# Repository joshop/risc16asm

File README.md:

# RISC-16

Assembler, emulator, and HDL for a custom 16-bit RISC-based instruction set.

## Usage

### Assembly

Suppose we have assembly code in `scripts/test_1.asm`. To assemble it into machine code:

```sh
python src/assemble.py scripts/test_1.asm [-o <output_file>]
```

If no output file is specified, it will default to `<basename>.bin`.

### Emulation

If the machine code is in `scripts/test_1.bin`, emulate it using

```sh
python src/interpret.py scripts/test_1.bin
```

### All-in-one

To do it all in one step, run

```sh
python src/run.py scripts/test_1.asm
```

## Assembly format

A program consists of a sequence of the following separated by newlines:

- Instructions of the form `op field, ...`, which emit their opcode
- Labels of the form `lab: `, which defines `lab` to be the current address
- Comments of the form `// comment text ended by a newline`
- Whitespace (which is ignored)
- Assembler directives
- Macros

Assembler directives include the following:

- `.word X` emits a single word (16 bits), `X`
- `.dword X` emits a double word (32 bits), `X`
- `.def Y X` defines a constant with value `X` called `Y`
- `.addr X` defines the current address to be `X`
- `.bin filename` emits all of the bytes in `filename`
- `.include filename` causes the assembler to process `filename`'s contents as if it was inserted into the file directly.
- `.macro pattern` defines a macro that translates any statement matched by the regex `pattern`. Statements until `.endmacro` are considered part of the macro. Macros can contain sub-macros that are already defined, as well as `.bin` and `.include` directives.

When instructions are assembled, immediates can be expressions with any of the following components:

- Constants in decimal, hexadecimal (`$` or `0x`) prefix, binary (`%` or `0b` prefix)
- Constants defined with `.def`
- Addresses of labels within the program
- `+`, `-`, `&`, `|`, `^`, `~`, `>>`, `<<` operators
  Example:

```
.macro li (r[0-7]), ([0-9]+)
lui \1, (\2) >> 8
addi \1, \1, (\2) & $ff
.endmacro
.addr 0
main:
  li r3, myfunction
  jalr r0, r3
.addr $1234
myfunction:
  // ... do something
```

Notes on syntax:

- `ecall <code>` can be used to trigger special hardware functions. They get encoded as a `jalr` instruction with nonzero immediate. The web interpreter is currently configured for the following ecall codes:
  - `1`: refresh display

## HDL

A SystemVerilog implementation of a CPU running this assembly exists in `src/hdl/`. Testbenches for this implementation exist in `src/hdl_sim/`.

## TODO

- [ ] Fix include file path tracing
- [ ] Figure out how context stuff works with respect to `.include` directives and document it

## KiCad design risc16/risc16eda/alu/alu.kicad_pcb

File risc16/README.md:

# RISC-16

Assembler, emulator, and HDL for a custom 16-bit RISC-based instruction set.

## Usage

### Assembly

Suppose we have assembly code in `scripts/test_1.asm`. To assemble it into machine code:

```sh
python src/assemble.py scripts/test_1.asm [-o <output_file>]
```

If no output file is specified, it will default to `<basename>.bin`.

### Emulation

If the machine code is in `scripts/test_1.bin`, emulate it using

```sh
python src/interpret.py scripts/test_1.bin
```

### All-in-one

To do it all in one step, run

```sh
python src/run.py scripts/test_1.asm
```

## Assembly format

A program consists of a sequence of the following separated by newlines:

- Instructions of the form `op field, ...`, which emit their opcode
- Labels of the form `lab: `, which defines `lab` to be the current address
- Comments of the form `// comment text ended by a newline`
- Whitespace (which is ignored)
- Assembler directives
- Macros

Assembler directives include the following:

- `.word X` emits a single word (16 bits), `X`
- `.dword X` emits a double word (32 bits), `X`
- `.def Y X` defines a constant with value `X` called `Y`
- `.addr X` defines the current address to be `X`
- `.bin filename` emits all of the bytes in `filename`
- `.include filename` causes the assembler to process `filename`'s contents as if it was inserted into the file directly.
- `.macro pattern` defines a macro that translates any statement matched by the regex `pattern`. Statements until `.endmacro` are considered part of the macro. Macros can contain sub-macros that are already defined, as well as `.bin` and `.include` directives.

When instructions are assembled, immediates can be expressions with any of the following components:

- Constants in decimal, hexadecimal (`$` or `0x`) prefix, binary (`%` or `0b` prefix)
- Constants defined with `.def`
- Addresses of labels within the program
- `+`, `-`, `&`, `|`, `^`, `~`, `>>`, `<<` operators
  Example:

```
.macro li (r[0-7]), ([0-9]+)
lui \1, (\2) >> 8
addi \1, \1, (\2) & $ff
.endmacro
.addr 0
main:
  li r3, myfunction
  jalr r0, r3
.addr $1234
myfunction:
  // ... do something
```

Notes on syntax:

- `ecall <code>` can be used to trigger special hardware functions. They get encoded as a `jalr` instruction with nonzero immediate. The web interpreter is currently configured for the following ecall codes:
  - `1`: refresh display

## HDL

A SystemVerilog implementation of a CPU running this assembly exists in `src/hdl/`. Testbenches for this implementation are in `src/hdl_sim/`.

## TODO

- [ ] Fix include file path tracing
- [ ] Figure out how context stuff works with respect to `.include` directives and document it

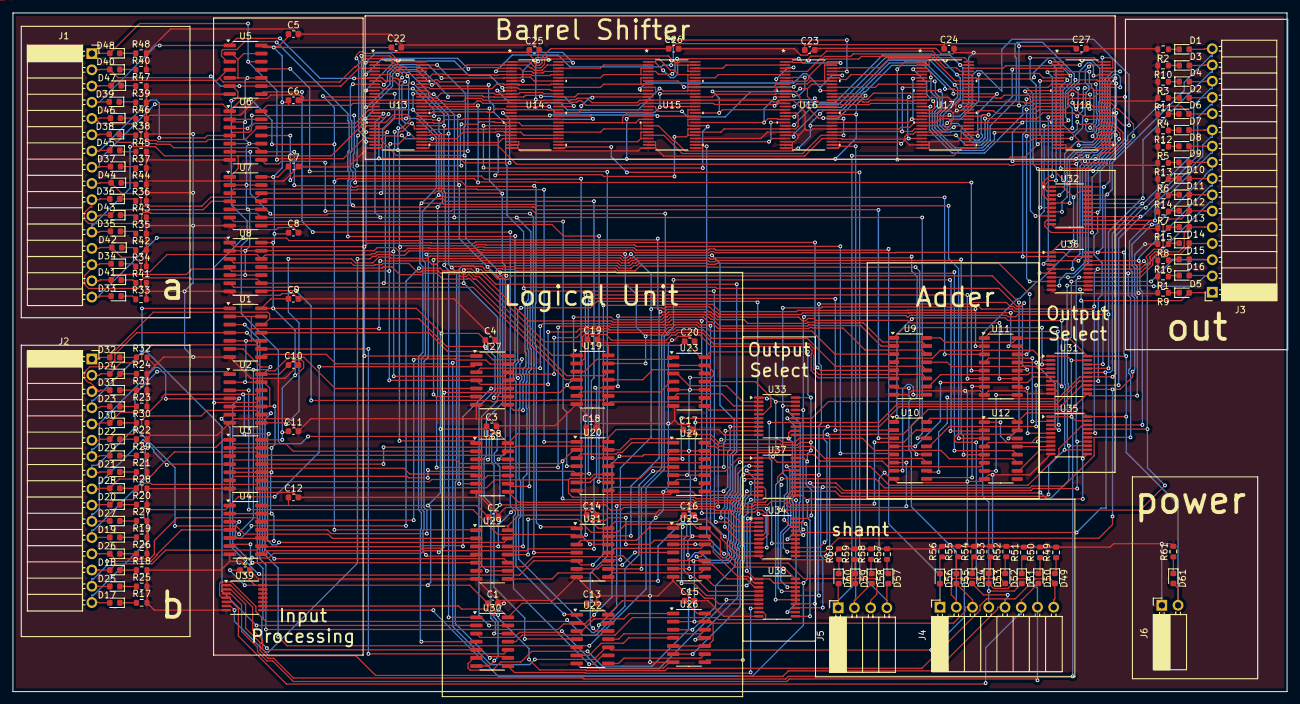
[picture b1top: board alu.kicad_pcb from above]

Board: 2 copper layers, 199.4 x 106.2 mm, 194 parts (0 on the bottom side), 322 nets.

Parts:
C1, C2, C3, C4, C5, C6, C7, C8, C9, C10, C11, C12, C13, C14, C15, C16, C17, C18, C19, C20, C22, C23, C24, C25, C26, C27: 0.1u; C_0603_1608Metric
C21: C; C_0603_1608Metric
D1, D2, D3, D4, D5, D6, D7, D8, D9, D10, D11, D12, D13, D14, D15, D16, D17, D18, D19, D20, D21, D22, D23, D24, D25, D26, D27, D28, D29, D30, D31, D32, D33, D34, D35, D36, D37, D38, D39, D40, D41, D42, D43, D44, D45, D46, D47, D48, D49, D50, D51, D52, D53, D54, D55, D56, D57, D58, D59, D60, D61: LED; LED_0603_1608Metric
J1, J2, J3: Conn_01x16; PinSocket_1x16_P2.54mm_Horizontal
J4: Conn_01x08; PinSocket_1x08_P2.54mm_Horizontal
J5: Conn_01x04; PinSocket_1x04_P2.54mm_Horizontal
J6: Conn_01x02; PinSocket_1x02_P2.54mm_Horizontal
R1, R2, R3, R4, R5, R6, R7, R8, R9, R10, R11, R12, R13, R14, R15, R16, R17, R18, R19, R20, R21, R22, R23, R24, R25, R26, R27, R28, R29, R30, R31, R32, R33, R34, R35, R36, R37, R38, R39, R40, R41, R42, R43, R44, R45, R46, R47, R48, R49, R50, R51, R52, R53, R54, R55, R56, R57, R58, R59, R60, R61: 1k; R_0603_1608Metric
U1, U2, U3, U4, U5, U6, U7, U8, U23, U24, U25, U26, U27, U28, U29, U30: 74HC86; SO-14_3.9x8.65mm_P1.27mm
U9, U10, U11, U12: 74LS283; SO-16_3.9x9.9mm_P1.27mm
U13, U14, U15, U16, U17, U18: SN74CBT16233DGGR; DGG56
U19, U20, U21, U22: 74HC00; SO-14_3.9x8.65mm_P1.27mm
U31, U32, U33, U34, U35, U36, U37, U38: 74AHC541; TSSOP-20_4.4x6.5mm_P0.65mm
U39: 74HC04; TSSOP-14_4.4x5mm_P0.65mm

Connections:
/!isAddSub: U31.1 (G1), U31.19 (G2), U35.1 (G1), U35.19 (G2), U39.2
/!isNand: U33.1 (G1), U33.19 (G2), U37.1 (G1), U37.19 (G2), U39.4
/!isShift: U32.1 (G1), U32.19 (G2), U36.1 (G1), U36.19 (G2), U39.6
/!isXor: U34.1 (G1), U34.19 (G2), U38.1 (G1), U38.19 (G2), U39.8
/A0: D33.2 (A), J1.16, U8.1, U9.5 (A1), U13.26 (16B2), U13.56 (1B1), U27.1
/A1: D41.2 (A), J1.15, U8.4, U9.3 (A2), U13.2 (2B1), U13.32 (15B2), U27.4
/A2: D34.2 (A), J1.14, U8.9, U9.14 (A3), U13.23 (14B2), U13.53 (3B1), U27.9
/A3: D42.2 (A), J1.13, U8.12, U9.12 (A4), U13.5 (4B1), U13.35 (13B2), U27.12
/A4: D35.2 (A), J1.12, U7.1, U10.5 (A1), U13.20 (12B2), U13.50 (5B1), U28.1
/A5: D43.2 (A), J1.11, U7.4, U10.3 (A2), U13.8 (6B1), U13.38 (11B2), U28.4
/A6: D36.2 (A), J1.10, U7.9, U10.14 (A3), U13.17 (10B2), U13.47 (7B1), U28.9
/A7: D44.2 (A), J1.9, U7.12, U10.12 (A4), U13.11 (8B1), U13.41 (9B2), U28.12
/A8: D37.2 (A), J1.8, U6.1, U11.5 (A1), U13.12 (8B2), U13.42 (9B1), U29.1
/A9: D45.2 (A), J1.7, U6.4, U11.3 (A2), U13.16 (10B1), U13.46 (7B2), U29.4
/A10: D38.2 (A), J1.6, U6.9, U11.14 (A3), U13.9 (6B2), U13.39 (11B1), U29.9
/A11: D46.2 (A), J1.5, U6.12, U11.12 (A4), U13.19 (12B1), U13.49 (5B2), U29.12
/A12: D39.2 (A), J1.4, U5.1, U12.5 (A1), U13.6 (4B2), U13.36 (13B1), U30.1
/A13: D47.2 (A), J1.3, U5.4, U12.3 (A2), U13.22 (14B1), U13.52 (3B2), U30.4
/A14: D40.2 (A), J1.2, U5.9, U12.14 (A3), U13.3 (2B2), U13.33 (15B1), U30.9
/A15: D48.2 (A), J1.1, U5.12, U12.12 (A4), U13.25 (16B1), U13.55 (1B2), U30.12
/A^neg0: U8.3, U19.1
/A^neg1: U8.6, U19.4
/A^neg2: U8.8, U19.9
/A^neg3: U8.11, U19.12
/A^neg4: U7.3, U20.1
/A^neg5: U7.6, U20.4
/A^neg6: U7.8, U20.9
/A^neg7: U7.11, U20.12
/A^neg8: U6.3, U21.1
/A^neg9: U6.6, U21.4
/A^neg10: U6.8, U21.9
/A^neg11: U6.11, U21.12
/A^neg12: U5.3, U22.1
/A^neg13: U5.6, U22.4
/A^neg14: U5.8, U22.9
/A^neg15: U5.11, U22.12
/B0: D17.2 (A), J2.16, U4.1, U27.2
/B1: D25.2 (A), J2.15, U4.4, U27.5
/B2: D18.2 (A), J2.14, U4.9, U27.10
/B3: D26.2 (A), J2.13, U4.12, U27.13
/B4: D19.2 (A), J2.12, U3.1, U28.2
/B5: D27.2 (A), J2.11, U3.4, U28.5
/B6: D20.2 (A), J2.10, U3.9, U28.10
/B7: D28.2 (A), J2.9, U3.12, U28.13
/B8: D21.2 (A), J2.8, U2.1, U29.2
/B9: D29.2 (A), J2.7, U2.4, U29.5
/B10: D22.2 (A), J2.6, U2.9, U29.10
/B11: D30.2 (A), J2.5, U2.12, U29.13
/B12: D23.2 (A), J2.4, U1.1, U30.2
/B13: D31.2 (A), J2.3, U1.4, U30.5
/B14: D24.2 (A), J2.2, U1.9, U30.10
/B15: D32.2 (A), J2.1, U1.12, U30.13
/B^neg0: U4.3, U9.6 (B1), U19.2
/B^neg1: U4.6, U9.2 (B2), U19.5
/B^neg2: U4.8, U9.15 (B3), U19.10
/B^neg3: U4.11, U9.11 (B4), U19.13
/B^neg4: U3.3, U10.6 (B1), U20.2
/B^neg5: U3.6, U10.2 (B2), U20.5
/B^neg6: U3.8, U10.15 (B3), U20.10
/B^neg7: U3.11, U10.11 (B4), U20.13
/B^neg8: U2.3, U11.6 (B1), U21.2
/B^neg9: U2.6, U11.2 (B2), U21.5
/B^neg10: U2.8, U11.15 (B3), U21.10
/B^neg11: U2.11, U11.11 (B4), U21.13
/B^neg12: U1.3, U12.6 (B1), U22.2
/B^neg13: U1.6, U12.2 (B2), U22.5
/B^neg14: U1.8, U12.15 (B3), U22.10
/B^neg15: U1.11, U12.11 (B4), U22.13
/addSub0: U9.4 (S1), U31.2 (A0)
/addSub1: U9.1 (S2), U31.3 (A1)
/addSub2: U9.13 (S3), U31.4 (A2)
/addSub3: U9.10 (S4), U31.5 (A3)
/addSub4: U10.4 (S1), U31.6 (A4)
/addSub5: U10.1 (S2), U31.7 (A5)
/addSub6: U10.13 (S3), U31.8 (A6)
/addSub7: U10.10 (S4), U31.9 (A7)
/addSub8: U11.4 (S1), U35.2 (A0)
/addSub9: U11.1 (S2), U35.3 (A1)
/addSub10: U11.13 (S3), U35.4 (A2)
/addSub11: U11.10 (S4), U35.5 (A3)
/addSub12: U12.4 (S1), U35.6 (A4)
/addSub13: U12.1 (S2), U35.7 (A5)
/addSub14: U12.13 (S3), U35.8 (A6)
/addSub15: U12.10 (S4), U35.9 (A7)
/carry01: U9.9 (C4), U10.7 (C0)
/carry12: U10.9 (C4), U11.7 (C0)
/carry23: U11.9 (C4), U12.7 (C0)
/isAddSub: D54.2 (A), J4.5, U39.1
/isNand: D53.2 (A), J4.7, U39.3
/isShift: D50.2 (A), J4.6, U39.5
/isXor: D49.2 (A), J4.8, U39.9
/nand0: U23.3, U33.2 (A0)
/nand1: U23.6, U33.3 (A1)
/nand2: U23.8, U33.4 (A2)
/nand3: U23.11, U33.5 (A3)
/nand4: U24.3, U33.6 (A4)
/nand5: U24.6, U33.7 (A5)
/nand6: U24.8, U33.8 (A6)
/nand7: U24.11, U33.9 (A7)
/nand8: U25.3, U37.2 (A0)
/nand9: U25.6, U37.3 (A1)
/nand10: U25.8, U37.4 (A2)
/nand11: U25.11, U37.5 (A3)
/nand12: U26.3, U37.6 (A4)
/nand13: U26.6, U37.7 (A5)
/nand14: U26.8, U37.8 (A6)
/nand15: U26.11, U37.9 (A7)
/negA: D56.2 (A), J4.1, U5.2, U5.5, U5.10, U5.13, U6.2, U6.5, U6.10, U6.13, U7.2, U7.5, U7.10, U7.13, U8.2, U8.5, U8.10, U8.13
/negB: D52.2 (A), J4.2, U1.2, U1.5, U1.10, U1.13, U2.2, U2.5, U2.10, U2.13, U3.2, U3.5, U3.10, U3.13, U4.2, U4.5, U4.10, U4.13, U9.7 (C0)
/negNand: D55.2 (A), J4.3, U23.2, U23.5, U23.10, U23.13, U24.2, U24.5, U24.10, U24.13, U25.2, U25.5, U25.10, U25.13, U26.2, U26.5, U26.10, U26.13
/out0: D1.2 (A), J3.16, U31.18 (Y0), U32.18 (Y0), U33.18 (Y0), U34.18 (Y0)
/out1: D3.2 (A), J3.15, U31.17 (Y1), U32.17 (Y1), U33.17 (Y1), U34.17 (Y1)
/out2: D4.2 (A), J3.14, U31.16 (Y2), U32.16 (Y2), U33.16 (Y2), U34.16 (Y2)
/out3: D2.2 (A), J3.13, U31.15 (Y3), U32.15 (Y3), U33.15 (Y3), U34.15 (Y3)
/out4: D6.2 (A), J3.12, U31.14 (Y4), U32.14 (Y4), U33.14 (Y4), U34.14 (Y4)
/out5: D7.2 (A), J3.11, U31.13 (Y5), U32.13 (Y5), U33.13 (Y5), U34.13 (Y5)
/out6: D8.2 (A), J3.10, U31.12 (Y6), U32.12 (Y6), U33.12 (Y6), U34.12 (Y6)
/out7: D9.2 (A), J3.9, U31.11 (Y7), U32.11 (Y7), U33.11 (Y7), U34.11 (Y7)
/out8: D10.2 (A), J3.8, U35.18 (Y0), U36.18 (Y0), U37.18 (Y0), U38.18 (Y0)
/out9: D11.2 (A), J3.7, U35.17 (Y1), U36.17 (Y1), U37.17 (Y1), U38.17 (Y1)
/out10: D12.2 (A), J3.6, U35.16 (Y2), U36.16 (Y2), U37.16 (Y2), U38.16 (Y2)
/out11: D13.2 (A), J3.5, U35.15 (Y3), U36.15 (Y3), U37.15 (Y3), U38.15 (Y3)
/out12: D14.2 (A), J3.4, U35.14 (Y4), U36.14 (Y4), U37.14 (Y4), U38.14 (Y4)
/out13: D15.2 (A), J3.3, U35.13 (Y5), U36.13 (Y5), U37.13 (Y5), U38.13 (Y5)
/out14: D16.2 (A), J3.2, U35.12 (Y6), U36.12 (Y6), U37.12 (Y6), U38.12 (Y6)
/out15: D5.2 (A), J3.1, U35.11 (Y7), U36.11 (Y7), U37.11 (Y7), U38.11 (Y7)
/rev?A0: U13.1 (1A), U14.56 (1B1)
/rev?A1: U13.54 (2A), U14.2 (2B1), U14.55 (1B2)
/rev?A2: U13.4 (3A), U14.3 (2B2), U14.53 (3B1)
/rev?A3: U13.51 (4A), U14.5 (4B1), U14.52 (3B2)
/rev?A4: U13.7 (5A), U14.6 (4B2), U14.50 (5B1)
/rev?A5: U13.48 (6A), U14.8 (6B1), U14.49 (5B2)
/rev?A6: U13.10 (7A), U14.9 (6B2), U14.47 (7B1)
/rev?A7: U13.45 (8A), U14.11 (8B1), U14.46 (7B2)
/rev?A8: U13.15 (9A), U14.12 (8B2), U14.42 (9B1)
/rev?A9: U13.40 (10A), U14.16 (10B1), U14.41 (9B2)
/rev?A10: U13.18 (11A), U14.17 (10B2), U14.39 (11B1)
/rev?A11: U13.37 (12A), U14.19 (12B1), U14.38 (11B2)
/rev?A12: U13.21 (13A), U14.20 (12B2), U14.36 (13B1)
/rev?A13: U13.34 (14A), U14.22 (14B1), U14.35 (13B2)
/rev?A14: U13.24 (15A), U14.23 (14B2), U14.33 (15B1)
/rev?A15: U13.31 (16A), U14.25 (16B1), U14.32 (15B2)
/sh1o0: U14.1 (1A), U15.56 (1B1)
/sh1o1: U14.54 (2A), U15.2 (2B1)
/sh1o2: U14.4 (3A), U15.53 (3B1), U15.55 (1B2)
/sh1o3: U14.51 (4A), U15.3 (2B2), U15.5 (4B1)
/sh1o4: U14.7 (5A), U15.50 (5B1), U15.52 (3B2)
/sh1o5: U14.48 (6A), U15.6 (4B2), U15.8 (6B1)
/sh1o6: U14.10 (7A), U15.47 (7B1), U15.49 (5B2)
/sh1o7: U14.45 (8A), U15.9 (6B2), U15.11 (8B1)
/sh1o8: U14.15 (9A), U15.42 (9B1), U15.46 (7B2)
/sh1o9: U14.40 (10A), U15.12 (8B2), U15.16 (10B1)
/sh1o10: U14.18 (11A), U15.39 (11B1), U15.41 (9B2)
/sh1o11: U14.37 (12A), U15.17 (10B2), U15.19 (12B1)
/sh1o12: U14.21 (13A), U15.36 (13B1), U15.38 (11B2)
/sh1o13: U14.34 (14A), U15.20 (12B2), U15.22 (14B1)
/sh1o14: U14.24 (15A), U15.33 (15B1), U15.35 (13B2)
/sh1o15: U14.31 (16A), U15.23 (14B2), U15.25 (16B1)
/sh2o0: U15.1 (1A), U16.56 (1B1)
/sh2o1: U15.54 (2A), U16.2 (2B1)
/sh2o2: U15.4 (3A), U16.53 (3B1)
/sh2o3: U15.51 (4A), U16.5 (4B1)
/sh2o4: U15.7 (5A), U16.50 (5B1), U16.55 (1B2)
/sh2o5: U15.48 (6A), U16.3 (2B2), U16.8 (6B1)
/sh2o6: U15.10 (7A), U16.47 (7B1), U16.52 (3B2)
/sh2o7: U15.45 (8A), U16.6 (4B2), U16.11 (8B1)
/sh2o8: U15.15 (9A), U16.42 (9B1), U16.49 (5B2)
/sh2o9: U15.40 (10A), U16.9 (6B2), U16.16 (10B1)
/sh2o10: U15.18 (11A), U16.39 (11B1), U16.46 (7B2)
/sh2o11: U15.37 (12A), U16.12 (8B2), U16.19 (12B1)
/sh2o12: U15.21 (13A), U16.36 (13B1), U16.41 (9B2)
/sh2o13: U15.34 (14A), U16.17 (10B2), U16.22 (14B1)
/sh2o14: U15.24 (15A), U16.33 (15B1), U16.38 (11B2)
/sh2o15: U15.31 (16A), U16.20 (12B2), U16.25 (16B1)
/sh4o0: U16.1 (1A), U17.56 (1B1)
/sh4o1: U16.54 (2A), U17.2 (2B1)
/sh4o2: U16.4 (3A), U17.53 (3B1)
/sh4o3: U16.51 (4A), U17.5 (4B1)
/sh4o4: U16.7 (5A), U17.50 (5B1)
/sh4o5: U16.48 (6A), U17.8 (6B1)
/sh4o6: U16.10 (7A), U17.47 (7B1)
/sh4o7: U16.45 (8A), U17.11 (8B1)
/sh4o8: U16.15 (9A), U17.42 (9B1), U17.55 (1B2)
/sh4o9: U16.40 (10A), U17.3 (2B2), U17.16 (10B1)
/sh4o10: U16.18 (11A), U17.39 (11B1), U17.52 (3B2)
/sh4o11: U16.37 (12A), U17.6 (4B2), U17.19 (12B1)
/sh4o12: U16.21 (13A), U17.36 (13B1), U17.49 (5B2)
/sh4o13: U16.34 (14A), U17.9 (6B2), U17.22 (14B1)
/sh4o14: U16.24 (15A), U17.33 (15B1), U17.46 (7B2)
/sh4o15: U16.31 (16A), U17.12 (8B2), U17.25 (16B1)
/sh8o0: U17.1 (1A), U18.26 (16B2), U18.56 (1B1)
/sh8o1: U17.54 (2A), U18.2 (2B1), U18.32 (15B2)
/sh8o2: U17.4 (3A), U18.23 (14B2), U18.53 (3B1)
/sh8o3: U17.51 (4A), U18.5 (4B1), U18.35 (13B2)
/sh8o4: U17.7 (5A), U18.20 (12B2), U18.50 (5B1)
/sh8o5: U17.48 (6A), U18.8 (6B1), U18.38 (11B2)
/sh8o6: U17.10 (7A), U18.17 (10B2), U18.47 (7B1)
/sh8o7: U17.45 (8A), U18.11 (8B1), U18.41 (9B2)
/sh8o8: U17.15 (9A), U18.12 (8B2), U18.42 (9B1)
/sh8o9: U17.40 (10A), U18.16 (10B1), U18.46 (7B2)
/sh8o10: U17.18 (11A), U18.9 (6B2), U18.39 (11B1)
/sh8o11: U17.37 (12A), U18.19 (12B1), U18.49 (5B2)
/sh8o12: U17.21 (13A), U18.6 (4B2), U18.36 (13B1)
/sh8o13: U17.34 (14A), U18.22 (14B1), U18.52 (3B2)
/sh8o14: U17.24 (15A), U18.3 (2B2), U18.33 (15B1)
/sh8o15: U17.31 (16A), U18.25 (16B1), U18.55 (1B2)
/shamt0: D57.2 (A), J5.4, U14.29 (SEL2), U14.30 (SEL1)
/shamt1: D59.2 (A), J5.3, U15.29 (SEL2), U15.30 (SEL1)
/shamt2: D58.2 (A), J5.2, U16.29 (SEL2), U16.30 (SEL1)
/shamt3: D60.2 (A), J5.1, U17.29 (SEL2), U17.30 (SEL1)
/shift0: U18.1 (1A), U32.2 (A0)
/shift1: U18.54 (2A), U32.3 (A1)
/shift2: U18.4 (3A), U32.4 (A2)
/shift3: U18.51 (4A), U32.5 (A3)
/shift4: U18.7 (5A), U32.6 (A4)
/shift5: U18.48 (6A), U32.7 (A5)
/shift6: U18.10 (7A), U32.8 (A6)
/shift7: U18.45 (8A), U32.9 (A7)
/shift8: U18.15 (9A), U36.2 (A0)
/shift9: U18.40 (10A), U36.3 (A1)
/shift10: U18.18 (11A), U36.4 (A2)
/shift11: U18.37 (12A), U36.5 (A3)
/shift12: U18.21 (13A), U36.6 (A4)
/shift13: U18.34 (14A), U36.7 (A5)
/shift14: U18.24 (15A), U36.8 (A6)
/shift15: U18.31 (16A), U36.9 (A7)
/shiftDirection: D51.2 (A), J4.4, U13.29 (SEL2), U13.30 (SEL1), U18.29 (SEL2), U18.30 (SEL1)
/xor0: U27.3, U34.2 (A0)
/xor1: U27.6, U34.3 (A1)
/xor2: U27.8, U34.4 (A2)
/xor3: U27.11, U34.5 (A3)
/xor4: U28.3, U34.6 (A4)
/xor5: U28.6, U34.7 (A5)
/xor6: U28.8, U34.8 (A6)
/xor7: U28.11, U34.9 (A7)
/xor8: U29.3, U38.2 (A0)
/xor9: U29.6, U38.3 (A1)
/xor10: U29.8, U38.4 (A2)
/xor11: U29.11, U38.5 (A3)
/xor12: U30.3, U38.6 (A4)
/xor13: U30.6, U38.7 (A5)
/xor14: U30.8, U38.8 (A6)
/xor15: U30.11, U38.9 (A7)
GND: C1.2, C2.2, C3.2, C4.2, C5.2, C6.2, C7.2, C8.2, C9.2, C10.2, C11.2, C12.2, C13.2, C14.2, C15.2, C16.2, C17.2, C18.2, C19.2, C20.2, C21.2, C22.2, C23.2, C24.2, C25.2, C26.2, C27.2, J6.1, R1.2, R2.2, R3.2, R4.2, R5.2, R6.2, R7.2, R8.2, R9.2, R10.2, R11.2, R12.2, R13.2, R14.2, R15.2, R16.2, R17.2, R18.2, R19.2, R20.2, R21.2, R22.2, R23.2, R24.2, R25.2, R26.2, R27.2, R28.2, R29.2, R30.2, R31.2, R32.2, R33.2, R34.2, R35.2, R36.2, R37.2, R38.2, R39.2, R40.2, R41.2, R42.2, R43.2, R44.2, R45.2, R46.2, R47.2, R48.2, R49.2, R50.2, R51.2, R52.2, R53.2, R54.2, R55.2, R56.2, R57.2, R58.2, R59.2, R60.2, R61.2, U1.7 (GND), U2.7 (GND), U3.7 (GND), U4.7 (GND), U5.7 (GND), U6.7 (GND), U7.7 (GND), U8.7 (GND), U9.8 (GND), U10.8 (GND), U11.8 (GND), U12.8 (GND), U13.13 (GND), U13.27 (TEST1), U13.28 (TEST2), U13.44 (GND), U14.13 (GND), U14.26 (16B2), U14.27 (TEST1), U14.28 (TEST2), U14.44 (GND), U15.13 (GND), U15.26 (16B2), U15.27 (TEST1), U15.28 (TEST2), U15.32 (15B2), U15.44 (GND), U16.13 (GND), U16.23 (14B2), U16.26 (16B2), U16.27 (TEST1), U16.28 (TEST2), U16.32 (15B2), U16.35 (13B2), U16.44 (GND), U17.13 (GND), U17.17 (10B2), U17.20 (12B2), U17.23 (14B2), U17.26 (16B2), U17.27 (TEST1), U17.28 (TEST2), U17.32 (15B2), U17.35 (13B2), U17.38 (11B2), U17.41 (9B2), U17.44 (GND), U18.13 (GND), U18.27 (TEST1), U18.28 (TEST2), U18.44 (GND), U19.7 (GND), U20.7 (GND), U21.7 (GND), U22.7 (GND), U23.7 (GND), U24.7 (GND), U25.7 (GND), U26.7 (GND), U27.7 (GND), U28.7 (GND), U29.7 (GND), U30.7 (GND), U31.10 (GND), U32.10 (GND), U33.10 (GND), U34.10 (GND), U35.10 (GND), U36.10 (GND), U37.10 (GND), U38.10 (GND), U39.7 (GND)
unnamed: D1.1 (K), R2.1
unnamed: D2.1 (K), R11.1
unnamed: D3.1 (K), R10.1
unnamed: D4.1 (K), R3.1
unnamed: D5.1 (K), R9.1
unnamed: D6.1 (K), R4.1
unnamed: D7.1 (K), R12.1
unnamed: D8.1 (K), R5.1
unnamed: D9.1 (K), R13.1
unnamed: D10.1 (K), R6.1
unnamed: D11.1 (K), R14.1
unnamed: D12.1 (K), R7.1
unnamed: D13.1 (K), R15.1
unnamed: D14.1 (K), R8.1
unnamed: D15.1 (K), R16.1
unnamed: D16.1 (K), R1.1
unnamed: D17.1 (K), R17.1
unnamed: D18.1 (K), R18.1
unnamed: D19.1 (K), R19.1
unnamed: D20.1 (K), R20.1
unnamed: D21.1 (K), R21.1
unnamed: D22.1 (K), R22.1
unnamed: D23.1 (K), R23.1
unnamed: D24.1 (K), R24.1
unnamed: D25.1 (K), R25.1
unnamed: D26.1 (K), R26.1
unnamed: D27.1 (K), R27.1
unnamed: D28.1 (K), R28.1
unnamed: D29.1 (K), R29.1
unnamed: D30.1 (K), R30.1
unnamed: D31.1 (K), R31.1
unnamed: D32.1 (K), R32.1
unnamed: D33.1 (K), R33.1
unnamed: D34.1 (K), R34.1
unnamed: D35.1 (K), R35.1
unnamed: D36.1 (K), R36.1
unnamed: D37.1 (K), R37.1
unnamed: D38.1 (K), R38.1
unnamed: D39.1 (K), R39.1
unnamed: D40.1 (K), R40.1
unnamed: D41.1 (K), R41.1
unnamed: D42.1 (K), R42.1
unnamed: D43.1 (K), R43.1
unnamed: D44.1 (K), R44.1
unnamed: D45.1 (K), R45.1
unnamed: D46.1 (K), R46.1
unnamed: D47.1 (K), R47.1
unnamed: D48.1 (K), R48.1
unnamed: D49.1 (K), R49.1
unnamed: D50.1 (K), R50.1
unnamed: D51.1 (K), R51.1
unnamed: D52.1 (K), R52.1
unnamed: D53.1 (K), R53.1
unnamed: D54.1 (K), R54.1
unnamed: D55.1 (K), R55.1
unnamed: D56.1 (K), R56.1
unnamed: D57.1 (K), R57.1
unnamed: D58.1 (K), R58.1
unnamed: D59.1 (K), R59.1
unnamed: D60.1 (K), R60.1
unnamed: D61.1 (K), R61.1
unnamed: U19.3, U23.1
unnamed: U19.6, U23.4
unnamed: U19.8, U23.9
unnamed: U19.11, U23.12
unnamed: U20.3, U24.1
unnamed: U20.6, U24.4
unnamed: U20.8, U24.9
unnamed: U20.11, U24.12
unnamed: U21.3, U25.1
unnamed: U21.6, U25.4
unnamed: U21.8, U25.9
unnamed: U21.11, U25.12
unnamed: U22.3, U26.1
unnamed: U22.6, U26.4
unnamed: U22.8, U26.9
unnamed: U22.11, U26.12
VCC: C1.1, C2.1, C3.1, C4.1, C5.1, C6.1, C7.1, C8.1, C9.1, C10.1, C11.1, C12.1, C13.1, C14.1, C15.1, C16.1, C17.1, C18.1, C19.1, C20.1, C21.1, C22.1, C23.1, C24.1, C25.1, C26.1, C27.1, D61.2 (A), J6.2, U1.14 (VCC), U2.14 (VCC), U3.14 (VCC), U4.14 (VCC), U5.14 (VCC), U6.14 (VCC), U7.14 (VCC), U8.14 (VCC), U9.16 (VCC), U10.16 (VCC), U11.16 (VCC), U12.16 (VCC), U13.14 (VCC), U13.43 (VCC), U14.14 (VCC), U14.43 (VCC), U15.14 (VCC), U15.43 (VCC), U16.14 (VCC), U16.43 (VCC), U17.14 (VCC), U17.43 (VCC), U18.14 (VCC), U18.43 (VCC), U19.14 (VCC), U20.14 (VCC), U21.14 (VCC), U22.14 (VCC), U23.14 (VCC), U24.14 (VCC), U25.14 (VCC), U26.14 (VCC), U27.14 (VCC), U28.14 (VCC), U29.14 (VCC), U30.14 (VCC), U31.20 (VCC), U32.20 (VCC), U33.20 (VCC), U34.20 (VCC), U35.20 (VCC), U36.20 (VCC), U37.20 (VCC), U38.20 (VCC), U39.14 (VCC)

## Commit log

2025-04-12 Implement constant parser
2025-04-13 Use regex library
2025-04-13 Begin implementing a line parser
2025-04-13 Move cpp out, we're using python rip
2025-04-13 Implement parse_const in python
2025-04-13 Implement python scaffolding
2025-04-13 Create interpreter
2025-04-15 Implement interpreter v1
2025-04-15 Revise readme, delete cpp files
2025-04-15 Support arbitrary width constants
2025-04-15 Implement up to ALU_SH instructions
2025-04-15 Implement BR-type
2025-04-15 Implement load and store word in assembler
2025-04-15 Finish assembler?
2025-04-15 Finish assembler ??
2025-04-16 Reorganize file structure a bit
2025-04-16 Implement interpreter ??
2025-04-16 Assemble only necessary bytes
2025-04-16 Pull out innterpreter
2025-04-16 Pull out interpreter
2025-04-16 Implement labels
2025-04-18 Add more debugging logs
2025-04-18 Fix b-type instructions
2025-04-18 Separate assemble program main method into two
2025-04-18 Specify instructions in readme
2025-04-18 Remove assembled .bin files (oops)
2025-04-19 Get macros to work ?? hopefully ??
2025-04-19 Implement max cycles
2025-04-19 Fix addi and nandi instructions, also h' and b' because visibility
2025-04-19 Fix case statement in base inst parser
2025-04-19 Add register aliases, add more formatting options
2025-04-19 Restrict base formatting to widths needed for 2^16
2025-04-19 Fix add sub case statements
2025-04-19 Fix load/store word
2025-04-19 Fix store instruction execution
2025-04-20 Implement .include in a scuffed way
2025-04-20 Do .include and .macro another way
2025-04-20 Add file path to assembly logs, update readme
2025-04-20 Actually fix the readme
2025-04-20 Fix jalr to jump first then link
2025-04-20 Fix jalr in execute to jump first then link
2025-04-20 Write a bunch of tests
2025-04-20 Assemble alu_al correctly
2025-04-20 Write a primality test
2025-04-20 Fix shifting, parse_const real width check
2025-04-20 Fix nandi
2025-04-20 Write a program to find nth prime number
2025-04-30 Initialize web interpreter
2025-05-01 Finish interpreter
2025-05-01 Oops remove dump file
2025-05-01 Remove log element, fix mem filling
2025-05-04 Remove logs from web interpreter, add memory-filling script
2025-05-09 Initialize display module
2025-05-12 Fix xor bug, add display
2025-05-18 Change style to be minimal black-and-white
2025-05-18 Make display 32x48
2025-05-18 Fix critical bug in execute case
2025-05-18 Clean up log statements, field extraction
2025-05-18 Prevent fill_mem from writing its own code lol
2025-05-18 Get MMIO output working?
2025-05-18 Run on prime # of cycles
2025-05-18 Tidy up interface
2025-05-18 Fix critical bugs in display module
2025-05-18 Add play/pause step buttons
2025-05-18 Update the way the display refreshes
2025-05-18 Account for halting
2025-05-18 Enable .def and .addr to use labels/def
2025-05-18 Make it light mode
2025-05-19 Add mid frame buffer driver
2025-05-19 Add support for pixel averaging display
2025-05-19 Add support for syscalls and pixel averaging display
2025-05-19 Critical bugfix: nested .includes
2025-05-19 Extract display_driver to its own assembly file
2025-05-19 Rename tests folder
2025-05-19 Get bad apple working!!
2025-12-15 Start HDL implementation (untested)
2025-12-19 Add tests for ALU
2025-12-20 Rewrite ALU using block diagram
2026-06-22 Add a new variant (acc816, working name) with simpler ISA
2026-06-22 Reorganize under acc816/ and risc16/
2026-06-23 Start implementing decoder
